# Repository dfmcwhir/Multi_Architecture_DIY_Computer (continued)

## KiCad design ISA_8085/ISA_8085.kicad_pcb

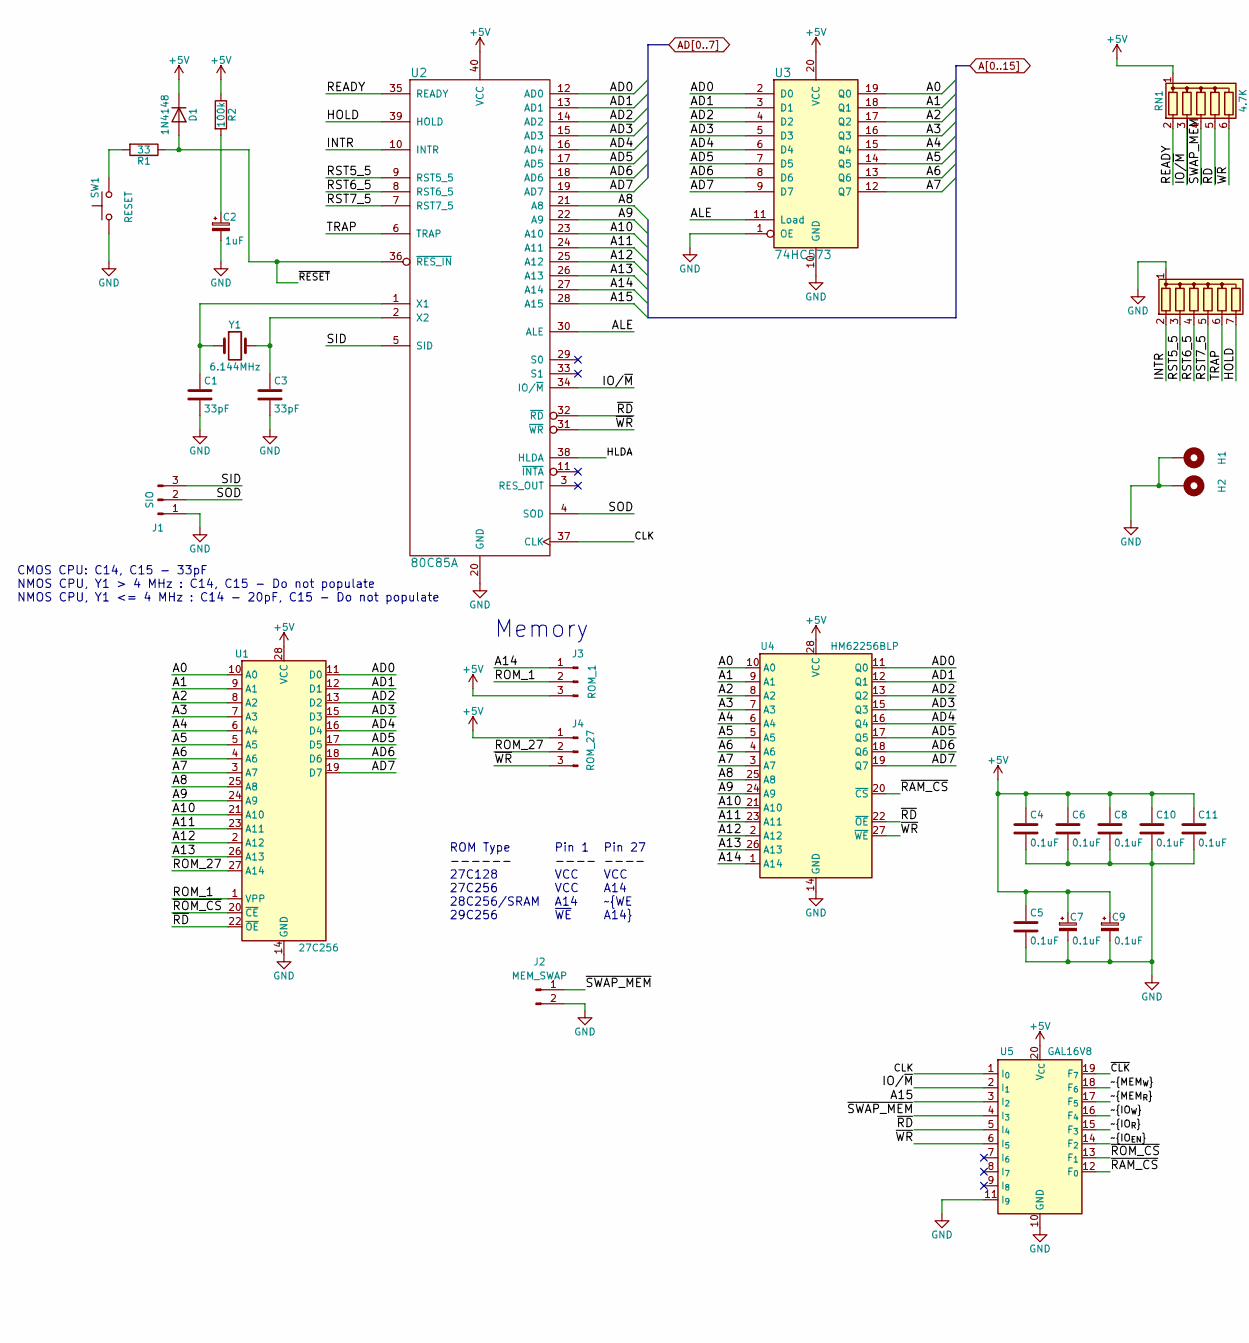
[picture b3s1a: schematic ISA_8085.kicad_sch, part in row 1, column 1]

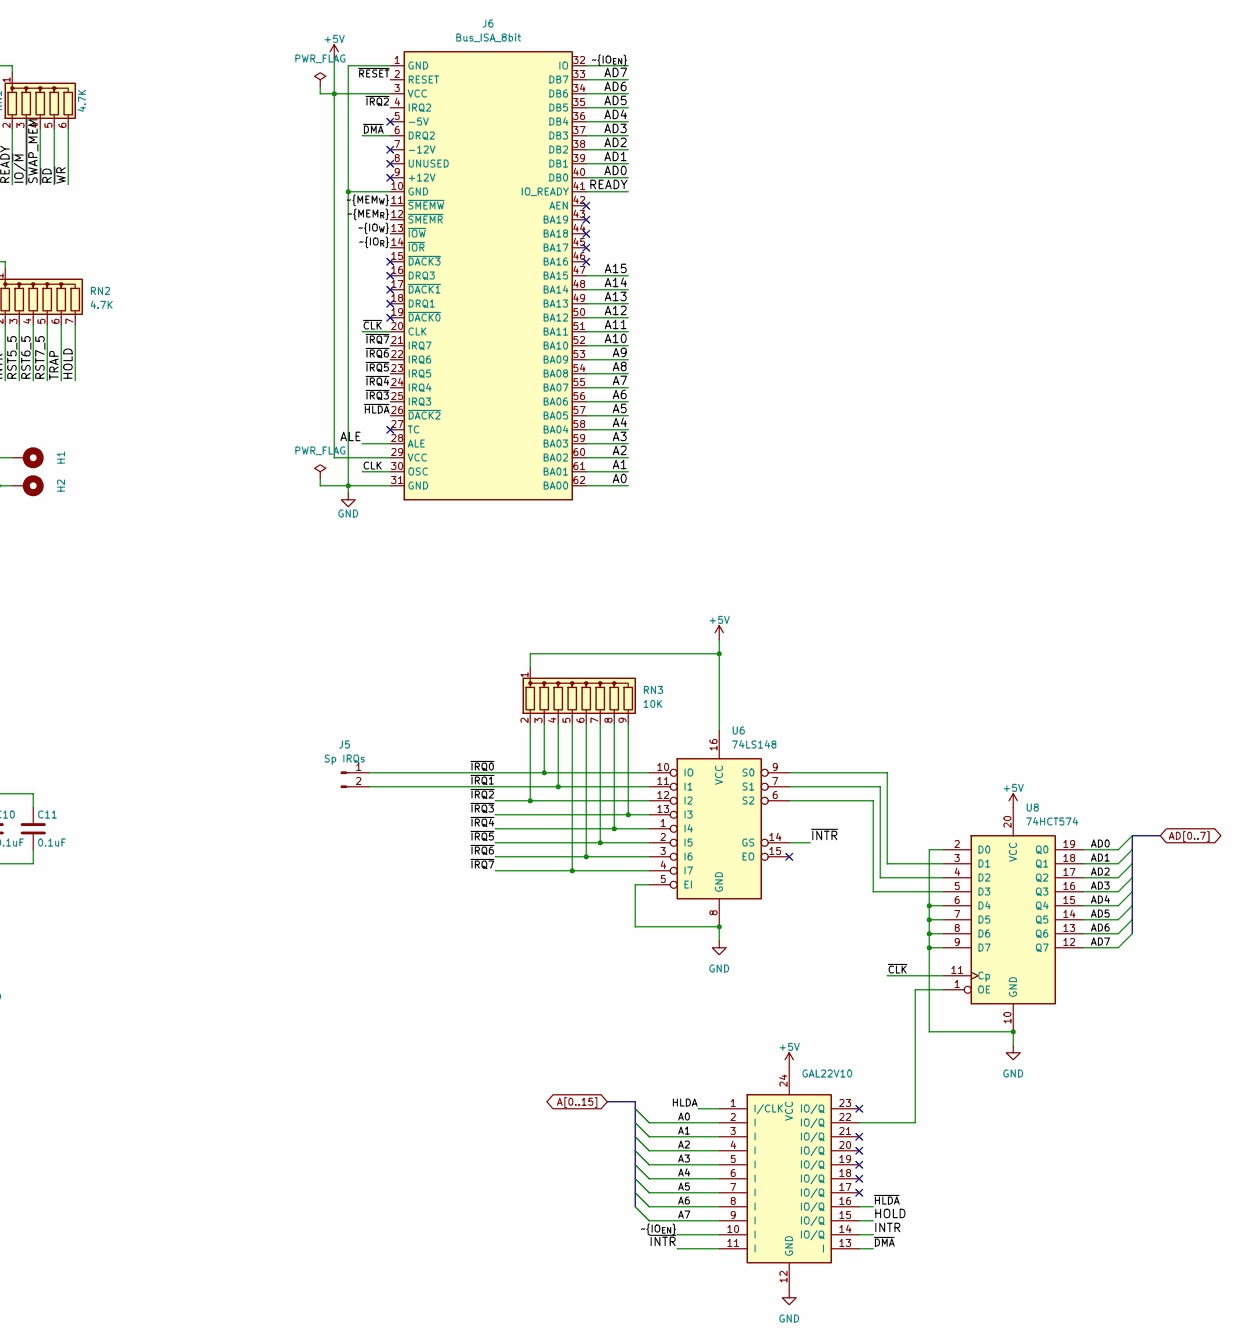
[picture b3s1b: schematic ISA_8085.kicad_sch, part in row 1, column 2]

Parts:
C1, C3: 33pF; C_Disc_D4.7mm_W2.5mm_P5.00mm
C2: 1uF; C_Disc_D4.7mm_W2.5mm_P5.00mm
C4, C5, C6, C7, C8, C9, C10, C11: 0.1uF; C_Disc_D4.7mm_W2.5mm_P5.00mm
D1: 1N4148; D_DO-15_P10.16mm_Horizontal
H1, H2: CONN_1; MountingHole_3.2mm_M3_ISO7380_Pad
J1: SIO; PinHeader_1x03_P2.54mm_Vertical
J2: MEM_SWAP; PinHeader_1x02_P2.54mm_Vertical
J3: ROM_1; PinHeader_1x03_P2.54mm_Vertical
J4: ROM_27; PinHeader_1x03_P2.54mm_Vertical
J5: Sp IRQs; PinHeader_1x02_P2.54mm_Vertical
J6: Bus_ISA_8bit; BUS_8-bit_ISA
R1: 33; R_Axial_DIN0207_L6.3mm_D2.5mm_P10.16mm_Horizontal
R2: 100k; R_Axial_DIN0207_L6.3mm_D2.5mm_P10.16mm_Horizontal
RN1: 4.7K; R_Array_SIP6
RN2: 4.7K; R_Array_SIP7
RN3: 10K; R_Array_SIP9
SW1: RESET; SW_PUSH_6mm
U1: 27C256; DIP-28_W15.24mm
U2: 80C85A; DIP-40_W15.24mm
U3: 74HC573; DIP-20_W7.62mm
U4: HM62256BLP; DIP-28_W15.24mm
U5: GAL16V8; DIP-20_W7.62mm
U6: 74LS148; DIP-16_W7.62mm
U7: GAL22V10; DIP-24_W7.62mm
U8: 74HCT574; DIP-20_W7.62mm
Y1: 6.144MHz; Crystal_HC18-U_Vertical

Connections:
+5V: C4.1, C5.1, C6.1, C7.1, C8.1, C9.1, C10.1, C11.1, D1.1 (K), J3.3, J4.1, J6.3 (VCC), J6.29 (VCC), R2.1, RN1.1 (common), RN3.1 (common), U1.28 (VCC), U2.40 (VCC), U3.20 (VCC), U4.28 (VCC), U5.20 (V_{CC}), U6.16 (VCC), U7.24 (VCC), U8.20 (VCC)
/ALE: J6.28 (ALE), U2.30 (ALE), U3.11 (Load)
/CLK: J6.30 (OSC), U2.37 (CLK), U5.1 (I_{0})
/HLDA: U2.38 (HLDA), U7.1 (I/CLK)
/HOLD: RN2.7 (R6), U2.39 (HOLD), U7.15 (IO/Q)
/INTR: RN2.2 (R1), U2.10 (INTR), U7.14 (IO/Q)
/IO/~M: RN1.3 (R2), U2.34 (IO/~M), U5.2 (I_{1})
/READY: J6.41 (IO_READY), RN1.2 (R1), U2.35 (READY)
/ROM_1: J3.2, U1.1 (VPP)
/ROM_27: J4.2, U1.27 (A14)
/RST5_5: RN2.3 (R2), U2.9 (RST5_5)
/RST6_5: RN2.4 (R3), U2.8 (RST6_5)
/RST7_5: RN2.5 (R4), U2.7 (RST7_5)
/SID: J1.3, U2.5 (SID)
/SOD: J1.2, U2.4 (SOD)
/TRAP: RN2.6 (R5), U2.6 (TRAP)
/~CLK: J6.20 (CLK), U5.19 (F_{7}), U8.11 (Cp)
/~DMA: J6.6 (DRQ2), U7.13 (I)
/~HLDA: J6.26 (~DACK2), U7.16 (IO/Q)
/~INTR: U6.14 (GS), U7.11 (I)
/~IO_{EN}: J6.32 (IO), U5.14 (F_{2}), U7.10 (I)
/~IO_{R}: J6.14 (~IOR), U5.15 (F_{3})
/~IO_{W}: J6.13 (~IOW), U5.16 (F_{4})
/~IRQ0: J5.1, RN3.3 (R2), U6.10 (IO)
/~IRQ1: J5.2, RN3.4 (R3), U6.11 (I1)
/~IRQ2: J6.4 (IRQ2), RN3.2 (R1), U6.12 (I2)
/~IRQ3: J6.25 (IRQ3), RN3.9 (R8), U6.13 (I3)
/~IRQ4: J6.24 (IRQ4), RN3.8 (R7), U6.1 (I4)
/~IRQ5: J6.23 (IRQ5), RN3.7 (R6), U6.2 (I5)
/~IRQ6: J6.22 (IRQ6), RN3.6 (R5), U6.3 (I6)
/~IRQ7: J6.21 (IRQ7), RN3.5 (R4), U6.4 (I7)
/~MEM_{R}: J6.12 (~SMEMR), U5.17 (F_{5})
/~MEM_{W}: J6.11 (~SMEMW), U5.18 (F_{6})
/~RAM_CS: U4.20 (~CS), U5.12 (F_{0})
/~RD: RN1.5 (R4), U1.22 (~OE), U2.32 (~RD), U4.22 (~OE), U5.5 (I_{4})
/~RESET: D1.2 (A), J6.2 (RESET), R1.1, U2.36 (~RES_IN)
/~ROM_CS: U1.20 (~CE), U5.13 (F_{1})
/~SWAP_MEM: J2.1, RN1.4 (R3), U5.4 (I_{3})
/~WR: J4.3, RN1.6 (R5), U2.31 (~WR), U4.27 (~WE), U5.6 (I_{5})
A0: J6.62 (BA00), U1.10 (A0), U3.19 (Q0), U4.10 (A0), U7.2 (I)
A1: J6.61 (BA01), U1.9 (A1), U3.18 (Q1), U4.9 (A1), U7.3 (I)
A2: J6.60 (BA02), U1.8 (A2), U3.17 (Q2), U4.8 (A2), U7.4 (I)
A3: J6.59 (BA03), U1.7 (A3), U3.16 (Q3), U4.7 (A3), U7.5 (I)
A4: J6.58 (BA04), U1.6 (A4), U3.15 (Q4), U4.6 (A4), U7.6 (I)
A5: J6.57 (BA05), U1.5 (A5), U3.14 (Q5), U4.5 (A5), U7.7 (I)
A6: J6.56 (BA06), U1.4 (A6), U3.13 (Q6), U4.4 (A6), U7.8 (I)
A7: J6.55 (BA07), U1.3 (A7), U3.12 (Q7), U4.3 (A7), U7.9 (I)
A8: J6.54 (BA08), U1.25 (A8), U2.21 (A8), U4.25 (A8)
A9: J6.53 (BA09), U1.24 (A9), U2.22 (A9), U4.24 (A9)
A10: J6.52 (BA10), U1.21 (A10), U2.23 (A10), U4.21 (A10)
A11: J6.51 (BA11), U1.23 (A11), U2.24 (A11), U4.23 (A11)
A12: J6.50 (BA12), U1.2 (A12), U2.25 (A12), U4.2 (A12)
A13: J6.49 (BA13), U1.26 (A13), U2.26 (A13), U4.26 (A13)
A14: J3.1, J6.48 (BA14), U2.27 (A14), U4.1 (A14)
A15: J6.47 (BA15), U2.28 (A15), U5.3 (I_{2})
AD0: J6.40 (DB0), U1.11 (D0), U2.12 (AD0), U3.2 (D0), U4.11 (Q0), U8.19 (Q0)
AD1: J6.39 (DB1), U1.12 (D1), U2.13 (AD1), U3.3 (D1), U4.12 (Q1), U8.18 (Q1)
AD2: J6.38 (DB2), U1.13 (D2), U2.14 (AD2), U3.4 (D2), U4.13 (Q2), U8.17 (Q2)
AD3: J6.37 (DB3), U1.15 (D3), U2.15 (AD3), U3.5 (D3), U4.15 (Q3), U8.16 (Q3)
AD4: J6.36 (DB4), U1.16 (D4), U2.16 (AD4), U3.6 (D4), U4.16 (Q4), U8.15 (Q4)
AD5: J6.35 (DB5), U1.17 (D5), U2.17 (AD5), U3.7 (D5), U4.17 (Q5), U8.14 (Q5)
AD6: J6.34 (DB6), U1.18 (D6), U2.18 (AD6), U3.8 (D6), U4.18 (Q6), U8.13 (Q6)
AD7: J6.33 (DB7), U1.19 (D7), U2.19 (AD7), U3.9 (D7), U4.19 (Q7), U8.12 (Q7)
GND: C1.2, C2.2, C3.2, C4.2, C5.2, C6.2, C7.2, C8.2, C9.2, C10.2, C11.2, H1.1 (1_1), H2.1 (1_1), J1.1, J2.2, J6.1 (GND), J6.10 (GND), J6.31 (GND), RN2.1 (common), SW1.1, U1.14 (GND), U2.20 (GND), U3.1 (OE), U3.10 (GND), U4.14 (GND), U5.10 (GND), U5.11 (I_{9}), U6.5 (EI), U6.8 (GND), U7.12 (GND), U8.2 (D0), U8.6 (D4), U8.7 (D5), U8.8 (D6), U8.9 (D7), U8.10 (GND)
unnamed: C2.1, R2.2
unnamed: R1.2, SW1.2
unnamed: C1.1, U2.1 (X1), Y1.1
unnamed: C3.1, U2.2 (X2), Y1.2
unnamed: U6.9 (S0), U8.3 (D1)
unnamed: U6.7 (S1), U8.4 (D2)
unnamed: U6.6 (S2), U8.5 (D3)
unnamed: U7.22 (IO/Q), U8.1 (OE)

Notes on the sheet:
Memory
Pin 1 ---- VCC VCC A14 ~{WE}
CMOS CPU: C14, C15 - 33pF NMOS CPU, Y1 > 4 MHz : C14, C15 - Do not populate NMOS CPU, Y1 <= 4 MHz : C14 - 20pF, C15 - Do not populate
ROM Type ------ 27C128 27C256 28C256/SRAM 29C256
Pin 27 ---- VCC A14 ~{WE A14}

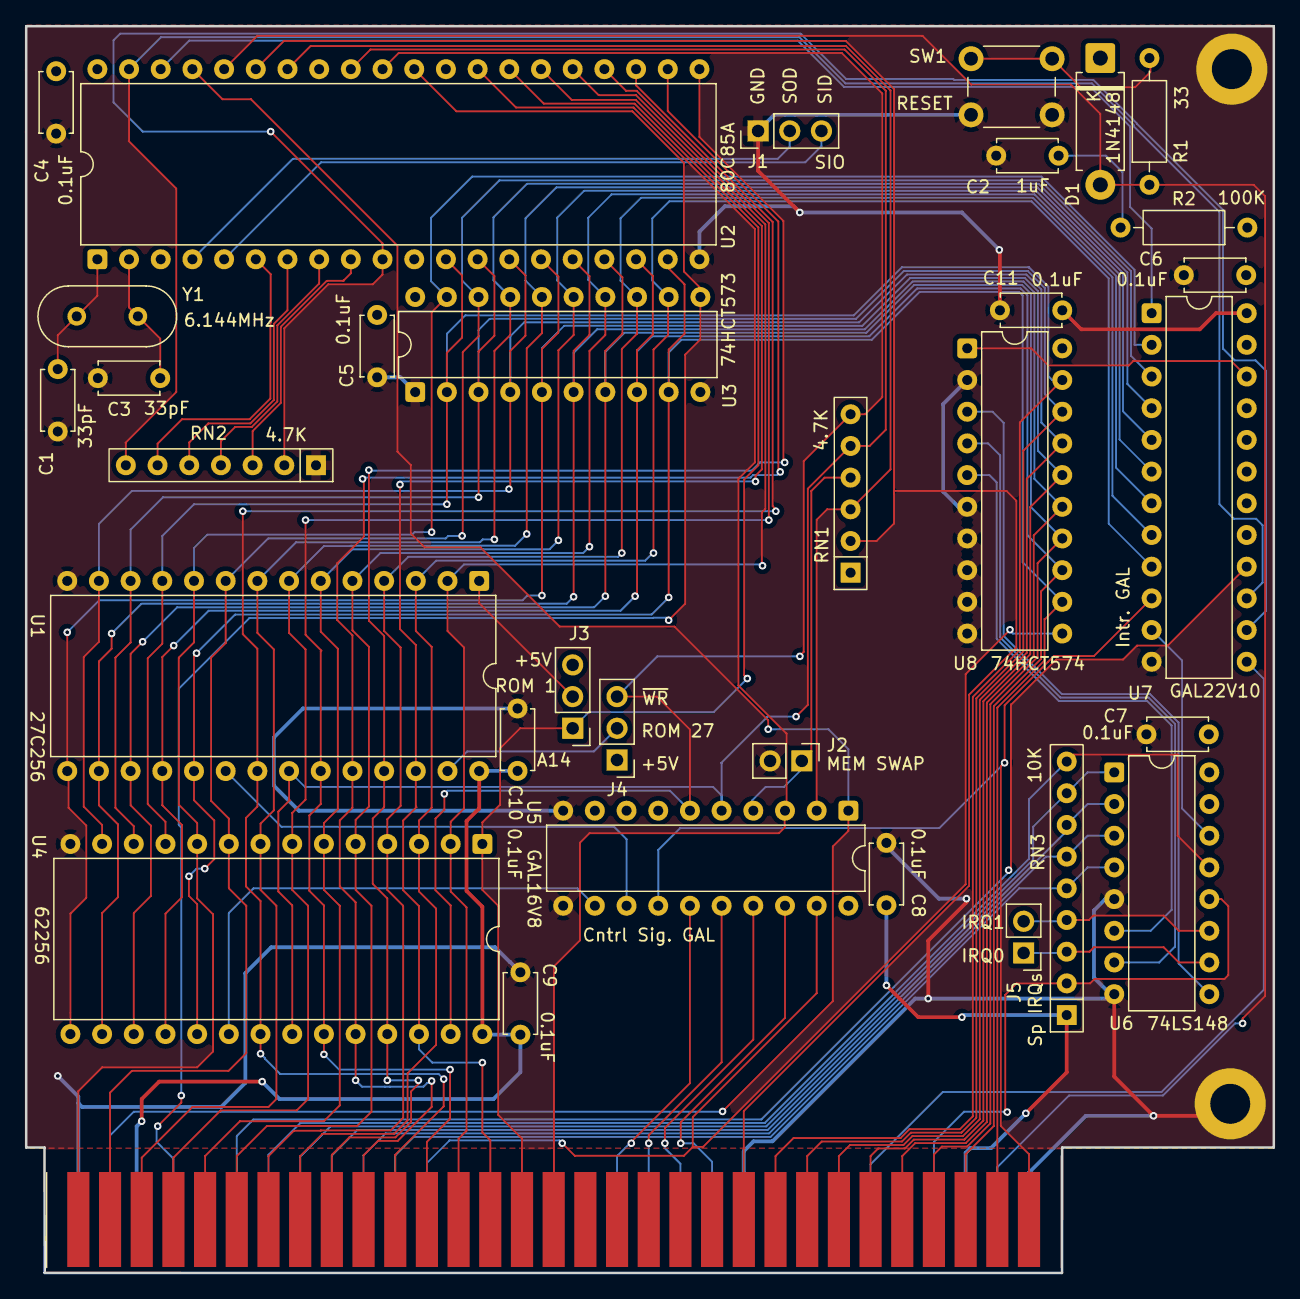
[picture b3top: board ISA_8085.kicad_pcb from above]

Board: 2 copper layers, 100.0 x 99.9 mm, 35 parts (0 on the bottom side), 72 nets.
